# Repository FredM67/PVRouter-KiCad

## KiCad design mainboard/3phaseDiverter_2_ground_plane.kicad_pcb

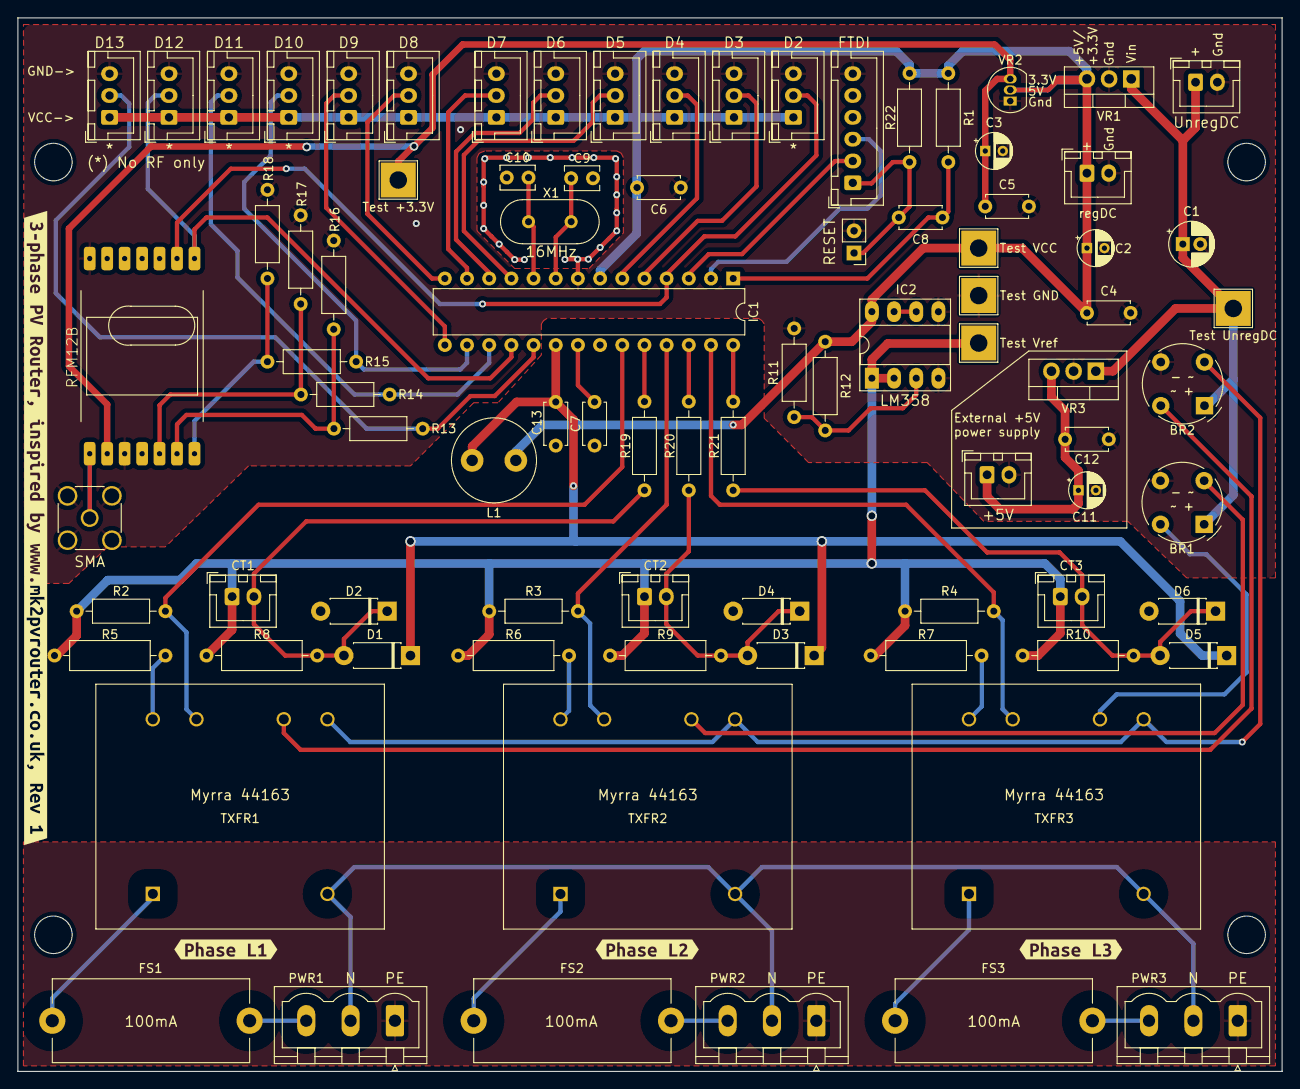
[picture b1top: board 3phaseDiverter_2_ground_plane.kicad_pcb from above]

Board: 2 copper layers, 144.8 x 120.6 mm, 90 parts (0 on the bottom side), 56 nets.

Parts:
BR1, BR2: B40R; Diode_Bridge_Round_D9.0mm
C1: 100uF; CP_Radial_D5.0mm_P2.00mm
C2, C3, C11: 10uF; CP_Radial_D4.0mm_P2.00mm
C4, C5, C6, C7, C8, C12, C13: 100nF; C_Disc_D4.7mm_W2.5mm_P5.00mm
C9, C10: 22pF; C_Disc_D3.8mm_W2.6mm_P2.50mm
CN9: SMA; SMA_Amphenol_132291-12_Vertical
CT1, CT2, CT3: Conn_01x02; JST_XH_B2B-XH-A_1x02_P2.50mm_Vertical
D1, D2, D3, D4, D5, D6: 1N4007; D_DO-41_SOD81_P7.62mm_Horizontal
FS1, FS2, FS3: 100mA; Fuseholder_Cylinder-5x20mm_Stelvio-Kontek_PTF78_Horizontal_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
IC1: ATmega328-P; DIP-28_W7.62mm
IC2: LM358; DIP-8_W7.62mm_Socket_LongPads
J0: FTDI; JST_XH_B6B-XH-A_1x06_P2.50mm_Vertical
J1: RESET; PinHeader_1x02_P2.54mm_Vertical_D0.85mm
J2: D2; JST_XH_B3B-XH-A_1x03_P2.50mm_Vertical
J3: D3; JST_XH_B3B-XH-A_1x03_P2.50mm_Vertical
J4: D4; JST_XH_B3B-XH-A_1x03_P2.50mm_Vertical
J5: D5; JST_XH_B3B-XH-A_1x03_P2.50mm_Vertical
J6: D6; JST_XH_B3B-XH-A_1x03_P2.50mm_Vertical
J7: D7; JST_XH_B3B-XH-A_1x03_P2.50mm_Vertical
J8: D8; JST_XH_B3B-XH-A_1x03_P2.50mm_Vertical
J9: D9; JST_XH_B3B-XH-A_1x03_P2.50mm_Vertical
J10: D10; JST_XH_B3B-XH-A_1x03_P2.50mm_Vertical
J11: D11; JST_XH_B3B-XH-A_1x03_P2.50mm_Vertical
J12: D12; JST_XH_B3B-XH-A_1x03_P2.50mm_Vertical
J13: D13; JST_XH_B3B-XH-A_1x03_P2.50mm_Vertical
J14: +5V; JST_XH_B2B-XH-A_1x02_P2.50mm_Vertical
J20: UnregDC; JST_XH_B2B-XH-A_1x02_P2.50mm_Vertical
J30: regDC; JST_XH_B2B-XH-A_1x02_P2.50mm_Vertical
L1: 10uH; L_Radial_D9.5mm_P5.00mm_Fastron_07HVP
PWR1, PWR2, PWR3: Conn_01x03_Phase; PhoenixContact_MSTBVA_2,5_3-G-5,08_1x03_P5.08mm_Vertical
R1: 47K; R_Axial_DIN0207_L6.3mm_D2.5mm_P10.16mm_Horizontal
R2, R3, R4: 180; R_Axial_DIN0207_L6.3mm_D2.5mm_P10.16mm_Horizontal
R5, R6, R7: 1K; R_Axial_DIN0309_L9.0mm_D3.2mm_P12.70mm_Horizontal
R8, R9, R10: 150; R_Axial_DIN0309_L9.0mm_D3.2mm_P12.70mm_Horizontal
R11, R12, R16, R17, R18: 10K; R_Axial_DIN0207_L6.3mm_D2.5mm_P10.16mm_Horizontal
R13, R14, R15: 4,7K; R_Axial_DIN0207_L6.3mm_D2.5mm_P10.16mm_Horizontal
R19, R20, R21: 1K; R_Axial_DIN0207_L6.3mm_D2.5mm_P10.16mm_Horizontal
R22: 1M; R_Axial_DIN0207_L6.3mm_D2.5mm_P10.16mm_Horizontal
RF1: RFM12B
TP0: Test UnregDC; TestPoint_THTPad_4.0x4.0mm_Drill2.0mm
TP1: Test Vref; TestPoint_THTPad_4.0x4.0mm_Drill2.0mm
TP2: Test VCC; TestPoint_THTPad_4.0x4.0mm_Drill2.0mm
TP3: Test GND; TestPoint_THTPad_4.0x4.0mm_Drill2.0mm
TP4: Test +3.3V; TestPoint_THTPad_4.0x4.0mm_Drill2.0mm
TXFR1, TXFR2, TXFR3: Myrra 44163; Transformer_Myrra_44163
VR1, VR3: L7805; TO-220-3_Vertical
VR2: MCP1700-3302E_TO92; TO-92_Inline
X1: 16MHz; Crystal_HC49-U_Vertical
kibuzzard-625015BB: G***; kibuzzard-625015BB
kibuzzard-625018AA: G***; kibuzzard-625018AA
kibuzzard-625018BF: G***; kibuzzard-625018BF
kibuzzard-62501737: G***; kibuzzard-62501737

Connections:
+3.3V: C3.1, C5.1, RF1.VDD, TP4.1, VR2.3 (VO)
+5V: C11.1, C12.1, J14.1, VR3.3 (OUT)
/D2: IC1.4 (INT0/PD2), J2.2, RF1.IRQ (DIO0/IRQ)
/D3: IC1.5 (INT1/PD3), J3.2
/D4: IC1.6 (XCK/T0/PD4), J4.2
/D5: IC1.11 (T1/PD5), J5.2
/D6: IC1.12 (AIN0/PD6), J6.2
/D7: IC1.13 (AIN1/PD7), J7.2
/D8: IC1.14 (ICP/PB0), J8.2
/D9: IC1.15 (OC1A/PB1), J9.2
/D10: IC1.16 (SS/OC1B/PB2), J10.2, R15.1
/D11: IC1.17 (MOSI/OC2/PB3), J11.2, R14.1
/D12: IC1.18 (MISO/PB4), J12.2, RF1.SDO
/D13: IC1.19 (SCK/PB5), J13.2, R13.1
A0: IC1.23 (ADC0/PC0), R2.1, TXFR1.9
A1: IC1.24 (ADC1/PC1), R19.2
A2: IC1.25 (ADC2/PC2), R3.1, TXFR2.9
A3: IC1.26 (ADC3/PC3), R20.2
A4: IC1.27 (ADC4/SDA/PC4), R4.1, TXFR3.9
A5: IC1.28 (ADC5/SDL/PC5), R21.2
AVCC: C13.1, D1.1 (K), D3.1 (K), D5.1 (K), IC1.20 (AVCC), L1.2
Earth: PWR1.1 (PE), PWR2.1 (PE), PWR3.1 (PE)
GND: BR1.3 (-), BR2.3 (-), C1.2, C2.2, C3.2, C4.2, C5.2, C6.1, C7.1, C9.1, C10.1, C11.2, C12.2, C13.2, CN9.2, D2.2 (A), D4.2 (A), D6.2 (A), IC1.8 (GND), IC1.22 (GND), IC2.4 (V-), IC2.5 (+), J0.6 (GND), J1.2, J2.3, J3.3, J4.3, J5.3, J6.3, J7.3, J8.3, J9.3, J10.3, J11.3, J12.3, J13.3, J14.2, J20.2, J30.2, R11.2, R16.1, R17.1, R18.1, RF1.GND, RF1.GND1, TP3.1, VR1.2 (GND), VR2.1 (GND), VR3.2 (GND)
NEUT: PWR1.2 (N), PWR2.2 (N), PWR3.2 (N), TXFR1.5, TXFR2.5, TXFR3.5
unnamed: BR1.2, TXFR2.7
unnamed: BR1.4, TXFR3.7
unnamed: BR2.2, TXFR1.6, TXFR2.6, TXFR3.6
unnamed: BR2.4, TXFR1.7
unnamed: C7.2, IC1.21 (AREF)
unnamed: C8.2, J0.1 (DTR), J1.1, R22.2
unnamed: C9.2, IC1.9 (PB6/XTAL1/TOSC1), X1.1
unnamed: C10.2, IC1.10 (PB7/XTAL2/TOSC), X1.2
unnamed: CN9.1, RF1.ANT
unnamed: CT1.2, D1.2 (A), D2.1 (K), R8.2, R19.1
unnamed: CT2.2, D3.2 (A), D4.1 (K), R9.2, R20.1
unnamed: CT3.2, D5.2 (A), D6.1 (K), R10.2, R21.1
unnamed: FS1.1, TXFR1.1
unnamed: FS1.2, PWR1.3 (L)
unnamed: FS2.1, TXFR2.1
unnamed: FS2.2, PWR2.3 (L)
unnamed: FS3.1, TXFR3.1
unnamed: FS3.2, PWR3.3 (L)
unnamed: IC2.3 (+), R11.1, R12.2
unnamed: IC2.6 (-), IC2.7
unnamed: R5.1, TXFR1.10
unnamed: R6.1, TXFR2.10
unnamed: R7.1, TXFR3.10
unnamed: R13.2, R16.2, RF1.SCK
unnamed: R14.2, R17.2, RF1.SDI
unnamed: R15.2, R18.2, RF1.SEL
RESET: C8.1, IC1.1 (PC6/~RESET), R1.2
RX: IC1.2 (RXD/PD0), J0.3 (TXO)
TX: IC1.3 (TXD/PD1), J0.2 (RXI)
UnregDC+: BR1.1 (+), BR2.1 (+), C1.1, J20.1, TP0.1, VR1.1 (IN), VR3.1 (IN)
VCC: C2.1, C4.1, C6.2, IC1.7 (VCC), IC2.8 (V+), J2.1, J3.1, J4.1, J5.1, J6.1, J7.1, J8.1, J9.1, J10.1, J11.1, J12.1, J13.1, J30.1, L1.1, R1.1, R12.1, R22.1, TP2.1, VR1.3 (OUT), VR2.2 (VI)
VREF: CT1.1, CT2.1, CT3.1, IC2.1, IC2.2 (-), R2.2, R3.2, R4.2, R5.2, R6.2, R7.2, R8.1, R9.1, R10.1, TP1.1

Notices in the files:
parts and their libraries:
Copyright 2021 Accelerated Designs. All rights reserved.
